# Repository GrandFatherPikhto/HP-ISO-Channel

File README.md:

# HP-ISO-Channel v0.99 — fabrication files

A small isolation board. It sits between the HiPIMS controller and the gate-driver boards
(HP-Power / HP-Channel). Generated with KiCad 10.0.8 from `HP-ISO-Channel-v099.kicad_pcb`.

## Board

| Parameter | Value |
|---|---|
| Layers | 2 |
| Size | 65.92 × 82.78 mm, rectangle |
| Thickness | 1.6 mm, FR4 |
| Copper | 35 µm (1 oz), both sides |
| Min track / clearance | 0.2 / 0.2 mm |
| Min drill | 0.3 mm (vias) |
| Vias (pad / drill) | 55 × 0.6 / 0.3, 16 × 0.8 / 0.4, 4 × 1.0 / 0.5 mm |
| Plated holes | components 0.7–1.0 mm; 2 × 3.5 mm (mounting holes H3, H4) |
| Non-plated holes | 2 × 3.5 mm (mounting holes H1, H2) — separate file |
| Slots / oblong holes | none |
| Components | top side only |
| Impedance control | not required |
| Surface finish, colours | not specified in the design — choose at order |

## Files

| File | Content |
|---|---|
| `HP-ISO-Channel-v099-F_Cu.gtl` | Top copper |
| `HP-ISO-Channel-v099-B_Cu.gbl` | Bottom copper |
| `HP-ISO-Channel-v099-F_Mask.gts` | Top solder mask |
| `HP-ISO-Channel-v099-B_Mask.gbs` | Bottom solder mask |
| `HP-ISO-Channel-v099-F_Silkscreen.gto` | Top silkscreen |
| `HP-ISO-Channel-v099-B_Silkscreen.gbo` | Bottom silkscreen (empty) |
| `HP-ISO-Channel-v099-F_Paste.gtp` | Top paste — stencil only |
| `HP-ISO-Channel-v099-B_Paste.gbp` | Bottom paste (empty) |
| `HP-ISO-Channel-v099-Edge_Cuts.gm1` | Board outline |
| `HP-ISO-Channel-v099-PTH.drl` | Plated holes, Excellon, metric |
| `HP-ISO-Channel-v099-NPTH.drl` | Non-plated holes, Excellon, metric |
| `HP-ISO-Channel-v099-job.gbrjob` | Gerber job file |

Gerber RS-274X (X2 attributes), units mm, format 4.6. All layers share the same origin.

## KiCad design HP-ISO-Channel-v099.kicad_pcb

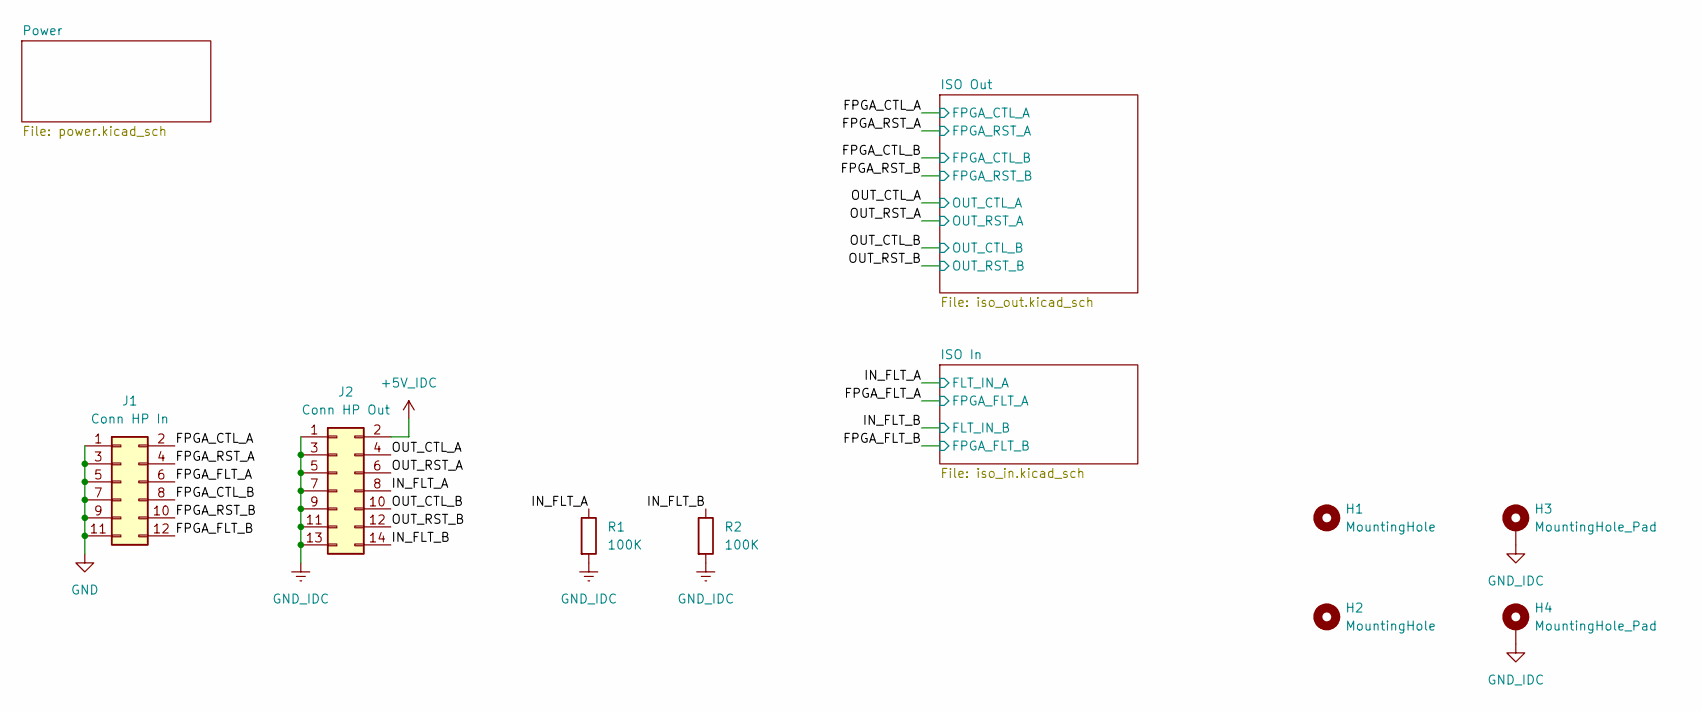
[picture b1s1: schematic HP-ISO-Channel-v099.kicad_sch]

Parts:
H1, H2: MountingHole; MountingHole_3.5mm
H3, H4: MountingHole_Pad; MountingHole_3.5mm_Pad
J1: Conn HP In; IDC-Header_2x06_P2.54mm_Vertical
J2: Conn HP Out; IDC-Header_2x07_P2.54mm_Vertical
R1, R2: 100K; R_0402_1005Metric_Pad0.72x0.64mm_HandSolder

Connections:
+5V_IDC: J2.2; also elsewhere on the board
/FPGA_CTL_A: J1.2; also elsewhere on the board
/FPGA_CTL_B: J1.8; also elsewhere on the board
/FPGA_FLT_A: J1.6; also elsewhere on the board
/FPGA_FLT_B: J1.12; also elsewhere on the board
/FPGA_RST_A: J1.4; also elsewhere on the board
/FPGA_RST_B: J1.10; also elsewhere on the board
/IN_FLT_A: J2.8, R1.1; also elsewhere on the board
/IN_FLT_B: J2.14, R2.1; also elsewhere on the board
/OUT_CTL_A: J2.4; also elsewhere on the board
/OUT_CTL_B: J2.10; also elsewhere on the board
/OUT_RST_A: J2.6; also elsewhere on the board
/OUT_RST_B: J2.12; also elsewhere on the board
GND: J1.1, J1.3, J1.5, J1.7, J1.9, J1.11; also elsewhere on the board
GND_IDC: H3.1 (1_1), H4.1 (1_1), J2.1, J2.3, J2.5, J2.7, J2.9, J2.11, J2.13, R1.2, R2.2; also elsewhere on the board

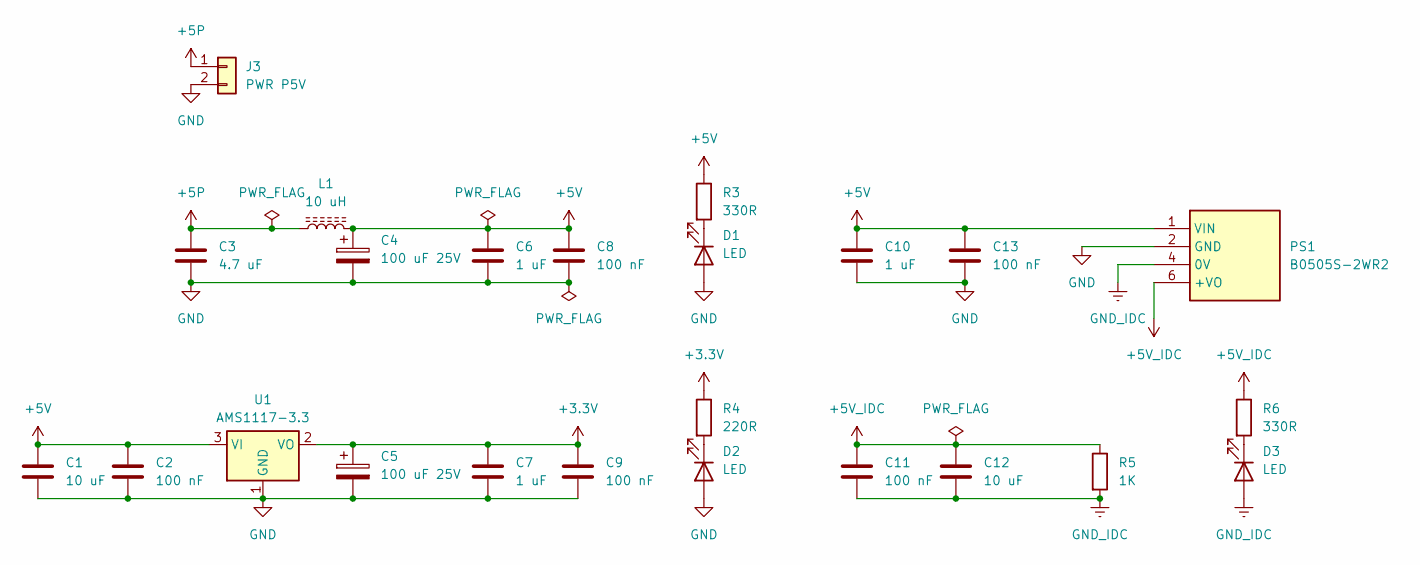
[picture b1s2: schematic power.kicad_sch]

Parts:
C1, C12: 10 uF; C_0603_1608Metric_Pad1.08x0.95mm_HandSolder
C2, C8, C9, C11, C13: 100 nF; C_0402_1005Metric_Pad0.74x0.62mm_HandSolder
C3: 4.7 uF; C_0603_1608Metric_Pad1.08x0.95mm_HandSolder
C4, C5: 100 uF 25V; CP_Radial_D5.0mm_P2.00mm
C6, C7, C10: 1 uF; C_0603_1608Metric_Pad1.08x0.95mm_HandSolder
D1, D2, D3: LED; LED_0805_2012Metric_Pad1.15x1.40mm_HandSolder
J3: PWR P5V; JST_XH_B2B-XH-A_1x02_P2.50mm_Vertical
L1: 10 uH; L_Bourns-SRN4018
PS1: B0505S-2WR2; SIP-4_19.65x7.05mm_P2.54mm; Manufacturer_Part_Number B0505S-2WR2
R3, R6: 330R; R_0402_1005Metric_Pad0.72x0.64mm_HandSolder
R4: 220R; R_0402_1005Metric_Pad0.72x0.64mm_HandSolder
R5: 1K; R_1206_3216Metric_Pad1.30x1.75mm_HandSolder
U1: AMS1117-3.3; SOT-223-3_TabPin2

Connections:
+3.3V: C5.1, C7.1, C9.1, R4.1, U1.2 (VO); also elsewhere on the board
+5P: C3.1, J3.1, L1.1
+5V: C1.1, C2.1, C4.1, C6.1, C8.1, C10.1, C13.1, L1.2, PS1.1 (VIN), R3.1, U1.3 (VI)
+5V_IDC: C11.1, C12.1, PS1.6 (+VO), R5.1, R6.1; also elsewhere on the board
GND: C1.2, C2.2, C3.2, C4.2, C5.2, C6.2, C7.2, C8.2, C9.2, C10.2, C13.2, D1.2 (A), D2.2 (A), J3.2, PS1.2 (GND), U1.1 (GND); also elsewhere on the board
GND_IDC: C11.2, C12.2, D3.2 (A), PS1.4 (0V), R5.2; also elsewhere on the board
unnamed: D1.1 (K), R3.2
unnamed: D2.1 (K), R4.2
unnamed: D3.1 (K), R6.2

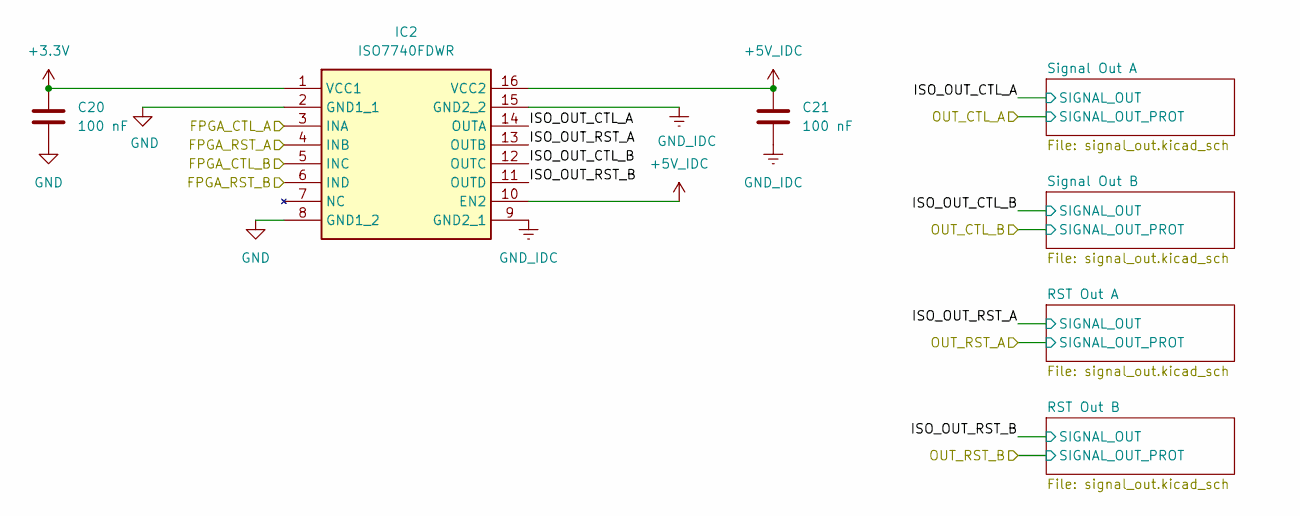
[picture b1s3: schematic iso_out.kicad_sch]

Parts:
C20, C21: 100 nF; C_0402_1005Metric_Pad0.74x0.62mm_HandSolder
IC2: ISO7740FDWR; SOIC-16W_7.5x10.3mm_P1.27mm; Manufacturer_Part_Number ISO7740FDWR; Mouser Part Number 595-ISO7740FDWR

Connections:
+3.3V: C20.1, IC2.1 (VCC1); also elsewhere on the board
+5V_IDC: C21.1, IC2.10 (EN2), IC2.16 (VCC2); also elsewhere on the board
/FPGA_CTL_A: IC2.3 (INA); also elsewhere on the board
/FPGA_CTL_B: IC2.5 (INC); also elsewhere on the board
/FPGA_RST_A: IC2.4 (INB); also elsewhere on the board
/FPGA_RST_B: IC2.6 (IND); also elsewhere on the board
/ISO Out/ISO_OUT_CTL_A: IC2.14 (OUTA); also elsewhere on the board
/ISO Out/ISO_OUT_CTL_B: IC2.12 (OUTC); also elsewhere on the board
/ISO Out/ISO_OUT_RST_A: IC2.13 (OUTB); also elsewhere on the board
/ISO Out/ISO_OUT_RST_B: IC2.11 (OUTD); also elsewhere on the board
GND: C20.2, IC2.2 (GND1_1), IC2.8 (GND1_2); also elsewhere on the board
GND_IDC: C21.2, IC2.9 (GND2_1), IC2.15 (GND2_2); also elsewhere on the board

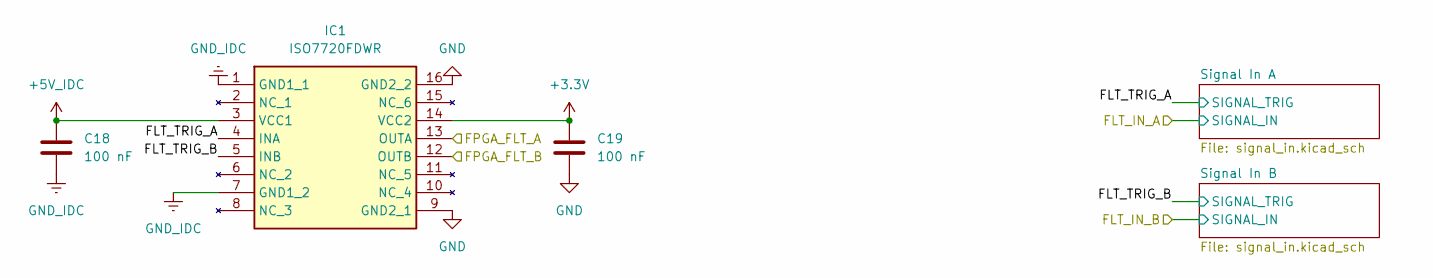
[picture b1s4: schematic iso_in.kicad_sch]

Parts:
C18, C19: 100 nF; C_0402_1005Metric_Pad0.74x0.62mm_HandSolder
IC1: ISO7720FDWR; SOIC-16W_7.5x10.3mm_P1.27mm; Manufacturer_Part_Number ISO7720FDWR; Mouser Part Number 595-ISO7720FDWR

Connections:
+3.3V: C19.1, IC1.14 (VCC2); also elsewhere on the board
+5V_IDC: C18.1, IC1.3 (VCC1); also elsewhere on the board
/FPGA_FLT_A: IC1.13 (OUTA); also elsewhere on the board
/FPGA_FLT_B: IC1.12 (OUTB); also elsewhere on the board
/ISO In/FLT_TRIG_A: IC1.4 (INA); also elsewhere on the board
/ISO In/FLT_TRIG_B: IC1.5 (INB); also elsewhere on the board
GND: C19.2, IC1.9 (GND2_1), IC1.16 (GND2_2); also elsewhere on the board
GND_IDC: C18.2, IC1.1 (GND1_1), IC1.7 (GND1_2); also elsewhere on the board

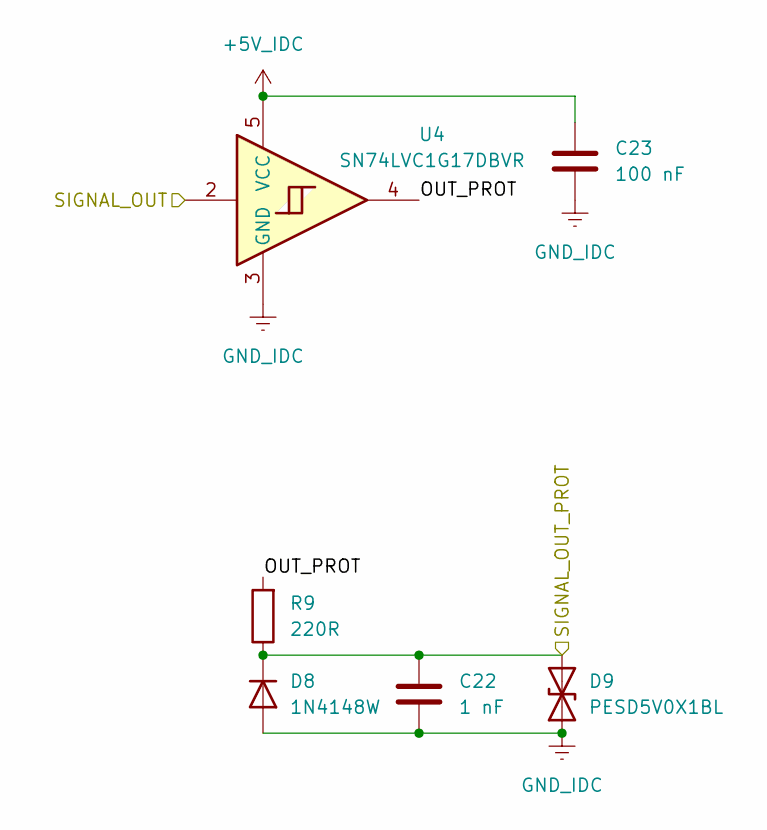
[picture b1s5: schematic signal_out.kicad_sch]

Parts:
C22: 1 nF; C_0402_1005Metric_Pad0.74x0.62mm_HandSolder
C23: 100 nF; C_0402_1005Metric_Pad0.74x0.62mm_HandSolder
D8: 1N4148W; D_SOD-123
D9: PESD5V0X1BL; D_SOD-882D
R9: 220R; R_0402_1005Metric_Pad0.72x0.64mm_HandSolder
U4: SN74LVC1G17DBVR; SOT-23-5

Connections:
+5V_IDC: C23.1, U4.5 (VCC); also elsewhere on the board
/ISO Out/ISO_OUT_CTL_A: U4.2; also elsewhere on the board
/ISO Out/Signal Out A/OUT_PROT: R9.2, U4.4
/OUT_CTL_A: C22.1, D8.1 (K), D9.2 (A2), R9.1; also elsewhere on the board
GND_IDC: C22.2, C23.2, D8.2 (A), D9.1 (A1), U4.3 (GND); also elsewhere on the board

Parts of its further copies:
C24, C26, C28: 1 nF; C_0402_1005Metric_Pad0.74x0.62mm_HandSolder
C25, C27, C29: 100 nF; C_0402_1005Metric_Pad0.74x0.62mm_HandSolder
D10, D12, D14: 1N4148W; D_SOD-123
D11, D13, D15: PESD5V0X1BL; D_SOD-882D
R10, R11, R12: 220R; R_0402_1005Metric_Pad0.72x0.64mm_HandSolder
U5, U6, U7: SN74LVC1G17DBVR; SOT-23-5

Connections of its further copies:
+5V_IDC: C25.1, C27.1, C29.1, U5.5 (VCC), U6.5 (VCC), U7.5 (VCC); also elsewhere on the board
/ISO Out/ISO_OUT_CTL_B: U5.2; also elsewhere on the board
/ISO Out/ISO_OUT_RST_A: U6.2; also elsewhere on the board
/ISO Out/ISO_OUT_RST_B: U7.2; also elsewhere on the board
/ISO Out/RST Out A/OUT_PROT: R11.2, U6.4
/ISO Out/RST Out B/OUT_PROT: R12.2, U7.4
/ISO Out/Signal Out B/OUT_PROT: R10.2, U5.4
/OUT_CTL_B: C24.1, D10.1 (K), D11.2 (A2), R10.1; also elsewhere on the board
/OUT_RST_A: C26.1, D12.1 (K), D13.2 (A2), R11.1; also elsewhere on the board
/OUT_RST_B: C28.1, D14.1 (K), D15.2 (A2), R12.1; also elsewhere on the board
GND_IDC: C24.2, C25.2, C26.2, C27.2, C28.2, C29.2, D10.2 (A), D11.1 (A1), D12.2 (A), D13.1 (A1), D14.2 (A), D15.1 (A1), U5.3 (GND), U6.3 (GND), U7.3 (GND); also elsewhere on the board

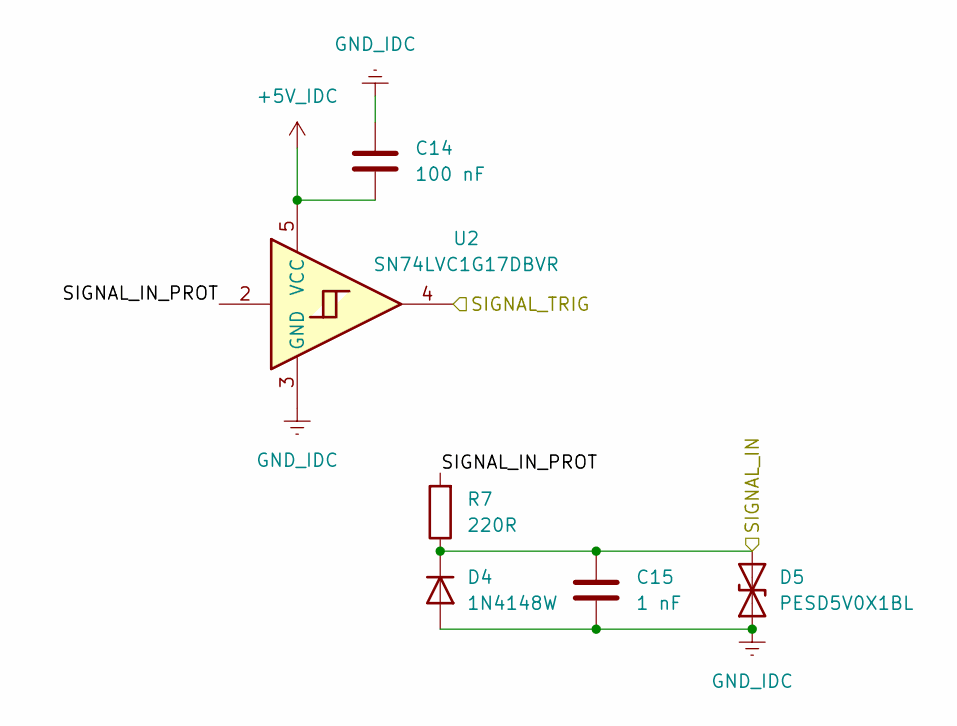
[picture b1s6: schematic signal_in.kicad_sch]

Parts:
C14: 100 nF; C_0402_1005Metric_Pad0.74x0.62mm_HandSolder
C15: 1 nF; C_0402_1005Metric_Pad0.74x0.62mm_HandSolder
D4: 1N4148W; D_SOD-123
D5: PESD5V0X1BL; D_SOD-882D
R7: 220R; R_0402_1005Metric_Pad0.72x0.64mm_HandSolder
U2: SN74LVC1G17DBVR; SOT-23-5

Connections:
+5V_IDC: C14.2, U2.5 (VCC); also elsewhere on the board
/IN_FLT_A: C15.1, D4.1 (K), D5.2 (A2), R7.1; also elsewhere on the board
/ISO In/FLT_TRIG_A: U2.4; also elsewhere on the board
/ISO In/Signal In A/SIGNAL_IN_PROT: R7.2, U2.2
GND_IDC: C14.1, C15.2, D4.2 (A), D5.1 (A1), U2.3 (GND); also elsewhere on the board

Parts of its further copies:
C16: 100 nF; C_0402_1005Metric_Pad0.74x0.62mm_HandSolder
C17: 1 nF; C_0402_1005Metric_Pad0.74x0.62mm_HandSolder
D6: 1N4148W; D_SOD-123
D7: PESD5V0X1BL; D_SOD-882D
R8: 220R; R_0402_1005Metric_Pad0.72x0.64mm_HandSolder
U3: SN74LVC1G17DBVR; SOT-23-5

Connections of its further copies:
+5V_IDC: C16.2, U3.5 (VCC); also elsewhere on the board
/IN_FLT_B: C17.1, D6.1 (K), D7.2 (A2), R8.1; also elsewhere on the board
/ISO In/FLT_TRIG_B: U3.4; also elsewhere on the board
/ISO In/Signal In B/SIGNAL_IN_PROT: R8.2, U3.2
GND_IDC: C16.1, C17.2, D6.2 (A), D7.1 (A1), U3.3 (GND); also elsewhere on the board

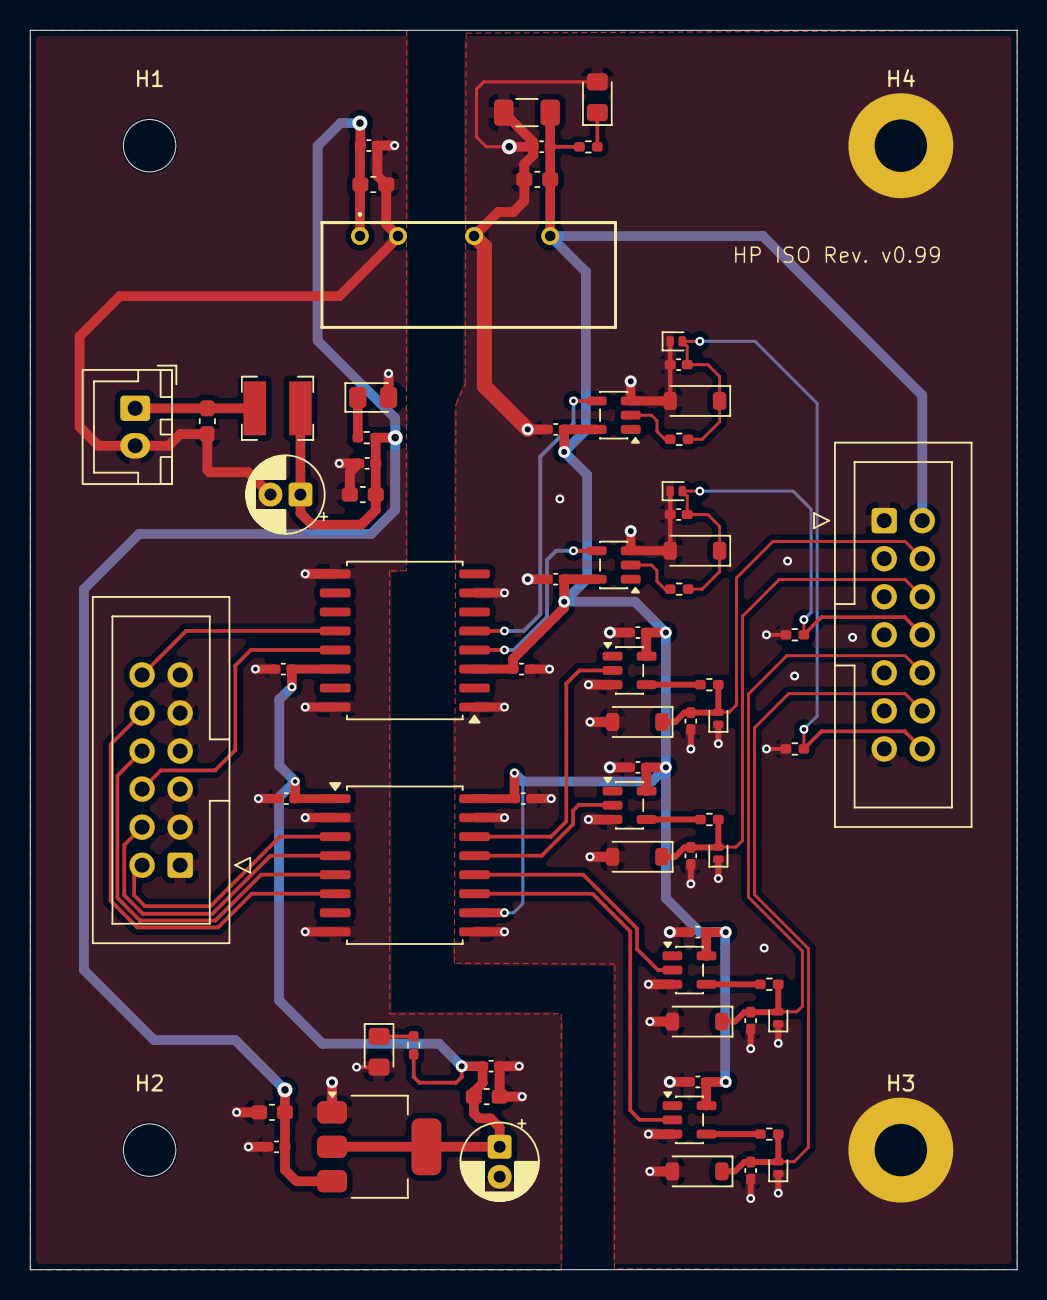
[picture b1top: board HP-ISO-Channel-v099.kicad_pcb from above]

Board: 2 copper layers, 65.9 x 82.7 mm, 74 parts (0 on the bottom side), 33 nets.
